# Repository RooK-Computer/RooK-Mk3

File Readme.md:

# RooK Mk3

RooK is a retro gaming console based on the Raspberry PI CM4. It has all the peripherials you need to be used as an old (modernish) console:

* HDMI for audio and video out.
* Barrel jack for 5V power input, because we love the simplicity of barrel jacks.
* an audio jack for, well... speakers!
* 4 USB ports for up to 4 modern gamepads.
* A cartridge slot!
* 3 Buttons to shut RooK down, exit the game and restart the game.

## How it all works

It's quite simple: instead of having an onboard SD card, the SD cards are installed onto separate PCBs for the cartridges. Once you put a cartridge in, RooK powers up and boots off the SD card in the cartridge.

Of course, unwrapping the SD cards can be tedious, so we built a cartridge reader.

It works out of the box with retropie, except for the three buttons. In this repository you find the software needed to enable those buttons. It's best done immediately after installing retropie, before you customize your setup.

## In this repository

There are 3 folders:

* software contains the sources for the .deb file to easily install overwatch and it's configuration. You'll find the .dep file in there as well, if you don't want to build it yourself. The source is compressed, as we have to ensure ownership and file privileges. Something git tends to ignore ;)
* PCBs contains all the designs for the PCBs involved: 
    * Cartridge - the PCB for cartridges
    * CartridgeReader - should be self-explanatory
    * KeyswitchCarrier - holds the switches for the three keys
    * Mainboard - the biggest of them.
    * Parts and CM4-Files are referenced in the aforementioned design files
* STLs contain the STL files for the case and the cartridge. You'll find our FreeCAD designs in there as well.

## I wanna build one!

Well for now, you have to produce and order the parts yourself. We're working on this. Stay tuned and keep an eye out at [rook.computer](https://rook.computer).

There is a building guide in the wiki.

## License

Unless noted otherwise this work is licensed under Creative Commons Attribution Share Alike 4.0 International.

`SPDX-License-Identifier:  CC-BY-SA-4.0`

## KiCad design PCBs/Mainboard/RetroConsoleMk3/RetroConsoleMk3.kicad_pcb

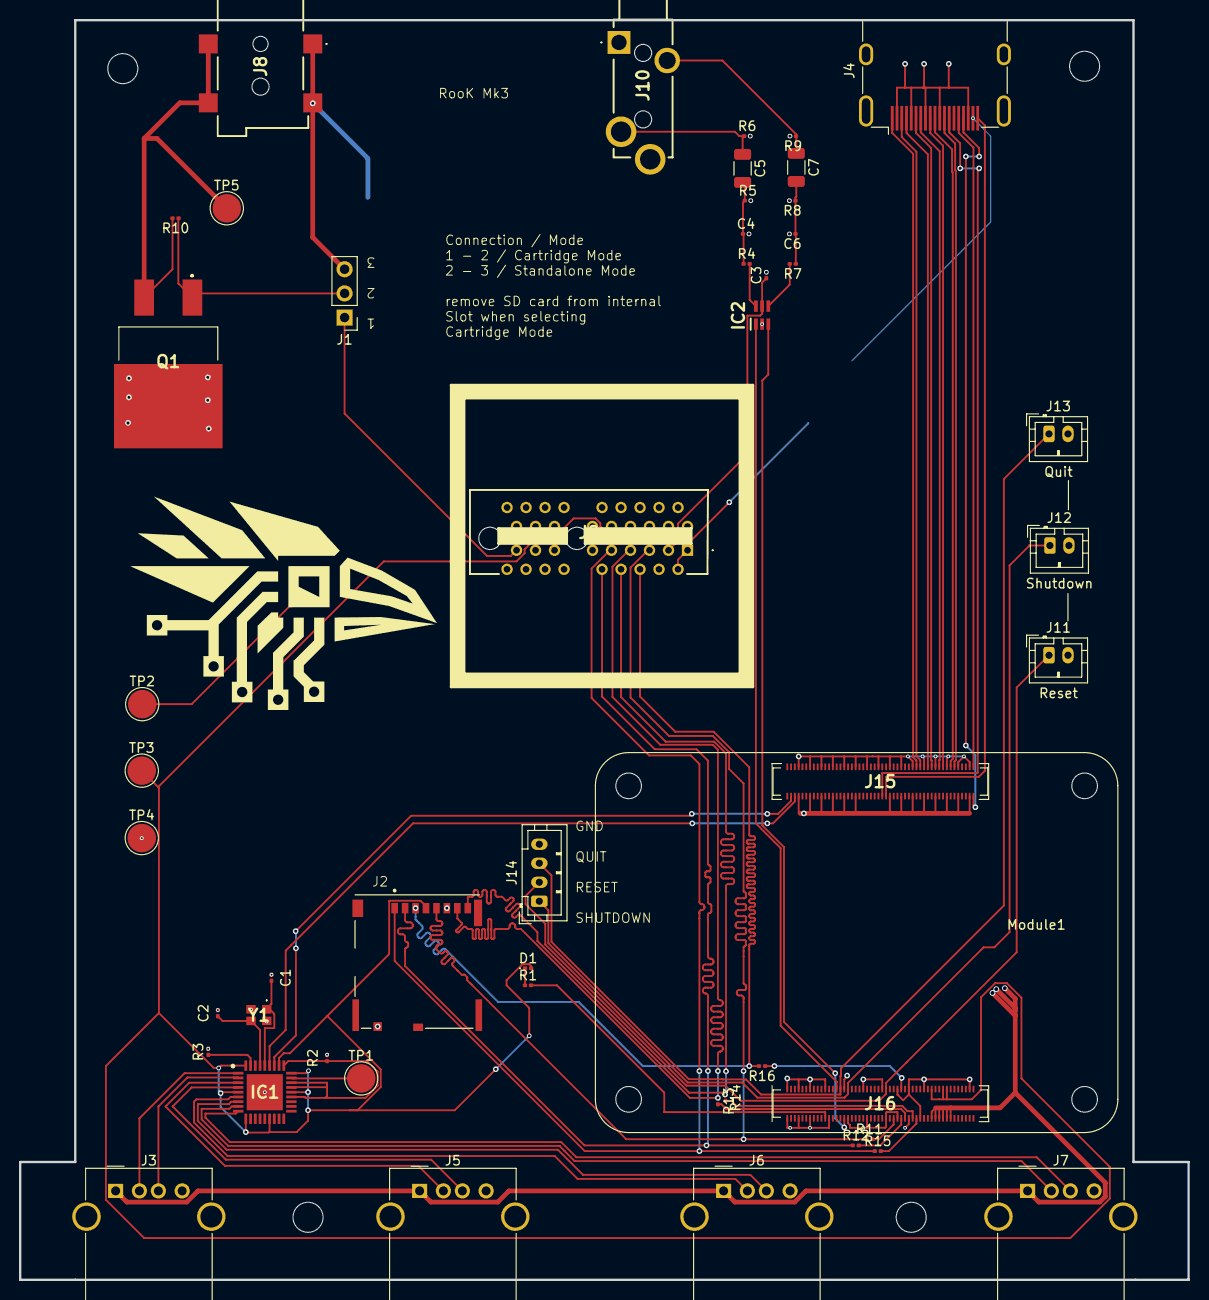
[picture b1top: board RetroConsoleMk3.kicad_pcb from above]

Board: 2 copper layers, 123.0 x 132.6 mm, 50 parts (0 on the bottom side), 58 nets.

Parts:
C1, C2: 14pF; C_0201_0603Metric
C3: 10nF; C_0201_0603Metric
C4, C6: 100nF; C_0201_0603Metric
C5, C7: 47uF; C_1206_3216Metric
D1: GREEN; LED_0201_0603Metric
IC1: USB2514B_M2; QFN50P600X600X100-37N-D
IC2: NC7WZ16P6X; SOT65P210X110-6N
J1: Conn_01x03_Socket; PinHeader_1x03_P2.54mm_Vertical
J2: Micro_SD_Card; SDCARD_MOLEX_503398-1892
J3, J5, J6, J7: USB_A; USB_A_Molex_67643_Horizontal
J4: HDMI_A_1.4; HDMI_A_Molex_208658-1001_Horizontal
J8: PJ-114AH-SMT-TR; PJ114AHSMTTR
J9: 1871058-1; 18710581
J10: SJ3-35083B-TR; SJ335083BTR
J11: Reset; JST_PH_B2B-PH-K_1x02_P2.00mm_Vertical
J12: Shutdown; JST_PH_B2B-PH-K_1x02_P2.00mm_Vertical
J13: Quit; JST_PH_B2B-PH-K_1x02_P2.00mm_Vertical
J14: Keys; JST_PH_B4B-PH-K_1x04_P2.00mm_Vertical
J15, J16: DF40C100DS04V51
Module1: ComputeModule4-CM4; Raspberry-Pi-4-Compute-Module
Q1: IRLZ34NSTRLPBF; IRF2804STRLPBF
R1: 1k; R_0201_0603Metric
R2: 100k; R_0201_0603Metric
R3: 12k (+/- 1%); R_0201_0603Metric
R4, R7: 220; R_0201_0603Metric
R5, R8: 100; R_0201_0603Metric
R6, R9: 1.8k; R_0201_0603Metric
R10: 10k; R_0201_0603Metric
R11, R12, R13, R14, R15, R16: 33; R_0201_0603Metric
TP1: USB RESET_N; TestPoint_Pad_D3.0mm
TP2: VCC; TestPoint_Pad_D3.0mm
TP3: 3V3; TestPoint_Pad_D3.0mm
TP4: GND; TestPoint_Pad_D3.0mm
TP5: GND_SUPPLY; TestPoint_Pad_D3.0mm
Y1: 830108208209

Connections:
3V3: C3.1, D1.2 (A), IC1.5 (VDDA33_1), IC1.10 (VDDA33_2), IC1.15 (VDD33_1), IC1.23 (VDD33_2), IC1.27 (VBUS_DET), IC1.29 (VDDA33_3), IC1.36 (VDDA33_4), IC2.5 (VCC), J2.4 (VDD), J9.A3, Module1.78 (GPIO_VREF(1.8v/3.3v_Input)), Module1.84 (+3.3v_(Output)), Module1.86 (+3.3v_(Output)), TP3.1
AUDIO_L: IC2.1 (A1), Module1.28 (GPIO13)
AUDIO_OUT_L: C5.1, J10.2 (TIP), R6.1
AUDIO_OUT_R: C7.1, J10.5 (RING), R9.1
AUDIO_R: IC2.3 (A2), Module1.31 (GPIO12)
CARD_PRESENT: J1.1, J9.A17
GND: C1.1, C2.2, C3.2, C4.2, C6.2, IC1.37 (EP), IC2.2 (GND), J2.6 (VSS), J2.9 (SHIELD), J3.4 (GND), J3.5 (Shield), J4.2 (D2S), J4.5 (D1S), J4.8 (D0S), J4.11 (CKS), J4.17 (GND), J5.4 (GND), J5.5 (Shield), J6.4 (GND), J6.5 (Shield), J7.4 (GND), J7.5 (Shield), J9.A4, J9.B1, J9.B2, J9.B3, J9.B4, J9.B5, J9.B6, J9.B7, J9.B8, J9.B9, J9.B10, J10.1 (SLEEVE), J11.2, J12.2, J13.2, J14.4, Module1.1 (GND), Module1.2 (GND), Module1.7 (GND), Module1.8 (GND), Module1.13 (GND), Module1.14 (GND), Module1.22 (GND), Module1.23 (GND), Module1.32 (GND), Module1.33 (GND), Module1.42 (GND), Module1.43 (GND), Module1.52 (GND), Module1.53 (GND), Module1.59 (GND), Module1.60 (GND), Module1.65 (GND), Module1.66 (GND), Module1.71 (GND), Module1.74 (GND), Module1.98 (GND), Module1.107 (GND), Module1.108 (GND), Module1.113 (GND), Module1.114 (GND), Module1.119 (GND), Module1.120 (GND), Module1.125 (GND), Module1.126 (GND), Module1.131 (GND), Module1.132 (GND), Module1.137 (GND), Module1.138 (GND), Module1.144 (GND), Module1.150 (GND), Module1.155 (GND), Module1.156 (GND), Module1.161 (GND), Module1.162 (GND), Module1.167 (GND), Module1.168 (GND), Module1.173 (GND), Module1.174 (GND), Module1.179 (GND), Module1.180 (GND), Module1.185 (GND), Module1.186 (GND), Module1.191 (GND), Module1.192 (GND), Module1.197 (GND), Module1.198 (GND), Q1.2 (D), R2.2, R3.2, R5.2, R6.2, R8.2, R9.2, TP4.1, Y1.2 (GND_1), Y1.4 (GND_2)
GND_SUPPLY: J8.2, J8.3, Q1.3 (S), R10.2, TP5.1
GPIO4: J11.1, J14.2, Module1.54 (GPIO4)
GPIO5: J12.1, J14.1, Module1.34 (GPIO5)
GPIO6: J13.1, J14.3, Module1.30 (GPIO6)
HDMI_CEC: J4.13 (CEC), Module1.151 (HDMI0_CEC)
HDMI_CK+: J4.10 (CK+), Module1.188 (HDMI0_CLK_P)
HDMI_CK-: J4.12 (CK-), Module1.190 (HDMI0_CLK_N)
HDMI_D0+: J4.7 (D0+), Module1.182 (HDMI0_TX0_P)
HDMI_D0-: J4.9 (D0-), Module1.184 (HDMI0_TX0_N)
HDMI_D1+: J4.4 (D1+), Module1.176 (HDMI0_TX1_P)
HDMI_D1-: J4.6 (D1-), Module1.178 (HDMI0_TX1_N)
HDMI_D2+: J4.1 (D2+), Module1.170 (HDMI0_TX2_P)
HDMI_D2-: J4.3 (D2-), Module1.172 (HDMI0_TX2_N)
HDMI_HEAC-: J4.19 (HPD/HEAC-), Module1.153 (HDMI0_HOTPLUG)
HDMI_SCL: J4.15 (SCL), Module1.200 (HDMI0_SCL)
HDMI_SDA: J4.16 (SDA), Module1.199 (HDMI0_SDA)
LED_ACTIVITY: Module1.21 (PI_nLED_Activity), R1.2
unnamed: C4.1, C5.2, R4.1, R5.1
unnamed: C6.1, C7.2, R7.1, R8.1
unnamed: D1.1 (K), R1.1
unnamed: IC1.26 (RESET_N), TP1.1
unnamed: IC1.1 (USBDM_DN1/PRT_DIS_M1), J3.2 (D-)
unnamed: IC1.3 (USBDM_DN2/PRT_DIS_M2), J5.2 (D-)
unnamed: IC1.6 (USBDM_DN3/PRT_DIS_M3), J6.2 (D-)
unnamed: IC1.8 (USBDM_DN4/PRT_DIS_M4), J7.2 (D-)
unnamed: IC1.2 (USBDP_DN1/PRT_DIS_P1), J3.3 (D+)
unnamed: IC1.4 (USBDP_DN2/PRT_DIS_P2), J5.3 (D+)
unnamed: IC1.7 (USBDP_DN3/PRT_DIS_P3), J6.3 (D+)
unnamed: IC1.9 (USBDP_DN4/PRT_DIS_P4), J7.3 (D+)
unnamed: IC2.6 (Y1), R4.2
unnamed: IC2.4 (Y2), R7.2
unnamed: Module1.57 (SD_CLK), R11.2
unnamed: Module1.62 (SD_CMD), R16.1
unnamed: Module1.63 (SD_DAT0), R13.2
unnamed: Module1.67 (SD_DAT1), R14.2
unnamed: Module1.69 (SD_DAT2), R15.2
unnamed: Module1.61 (SD_DAT3), R12.2
SD_CLK: J2.5 (CLK), J9.A5, R11.1
SD_CMD: J2.3 (CMD), J9.A6, R16.2
SD_DAT0: J2.7 (DAT0), J9.A7, R13.1
SD_DAT1: J2.8 (DAT1), J9.A8, R14.1
SD_DAT2: J2.1 (DAT2), J9.A9, R15.1
SD_DAT3: J2.2 (DAT3/CD), J9.A10, R12.1
SUPPLY_ENABLE: J1.2, Q1.1 (G), R10.1
USB_CFG_SEL0: IC1.22 (SDA/SMBDATA/NONREM1), IC1.24 (SCL/SMBCLK/CFG_SEL0), IC1.25 (HS_IND/CFG_SEL1), IC1.28 (SUSP_IND/LOCAL_PWR/NON_REM0), R2.1
USB_D+: IC1.31 (USBDP_UP), Module1.105 (USB2_P)
USB_D-: IC1.30 (USBDM_UP), Module1.103 (USB2_N)
USB_RBIAS: IC1.35 (RBIAS), R3.1
USB_XTAL_IN: C2.1, IC1.33 (XTALIN/CLKIN), Y1.3 (CRYSTAL_2)
USB_XTAL_OUT: C1.2, IC1.32 (XTALOUT), Y1.1 (CRYSTAL_1)
VCC: J1.3, J3.1 (VBUS), J4.18 (+5V), J5.1 (VBUS), J6.1 (VBUS), J7.1 (VBUS), J8.A1, J8.B1, J9.A1, J9.A2, Module1.77 (+5v_(Input)), Module1.79 (+5v_(Input)), Module1.81 (+5v_(Input)), Module1.83 (+5v_(Input)), Module1.85 (+5v_(Input)), Module1.87 (+5v_(Input)), TP2.1

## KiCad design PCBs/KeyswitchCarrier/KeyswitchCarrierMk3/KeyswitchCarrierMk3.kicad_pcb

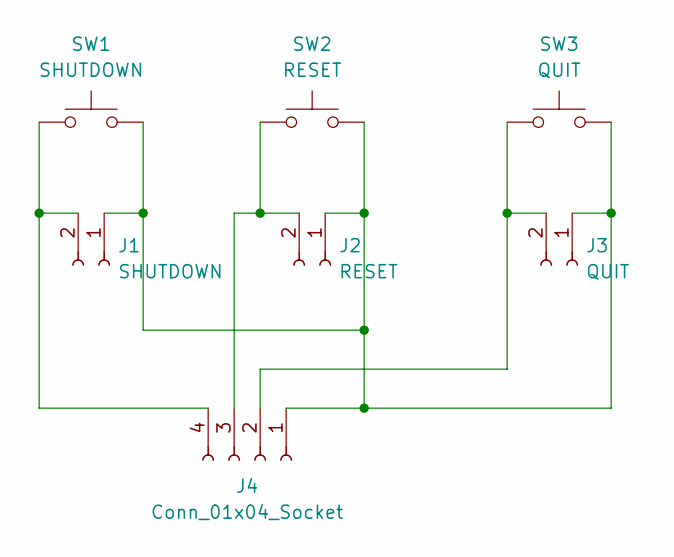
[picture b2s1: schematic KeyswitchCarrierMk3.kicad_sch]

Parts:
J1: SHUTDOWN; JST_PH_S2B-PH-K_1x02_P2.00mm_Horizontal
J2: RESET; JST_PH_S2B-PH-K_1x02_P2.00mm_Horizontal
J3: QUIT; JST_PH_S2B-PH-K_1x02_P2.00mm_Horizontal
J4: Conn_01x04_Socket; JST_PH_S4B-PH-K_1x04_P2.00mm_Horizontal
SW1: SHUTDOWN; SW_Cherry_MX_1.00u_PCB
SW2: RESET; SW_Cherry_MX_1.00u_PCB
SW3: QUIT; SW_Cherry_MX_1.00u_PCB

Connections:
unnamed: J1.1, J2.1, J3.1, J4.1, SW1.2, SW2.2, SW3.2
unnamed: J1.2, J4.4, SW1.1
unnamed: J2.2, J4.3, SW2.1
unnamed: J3.2, J4.2, SW3.1

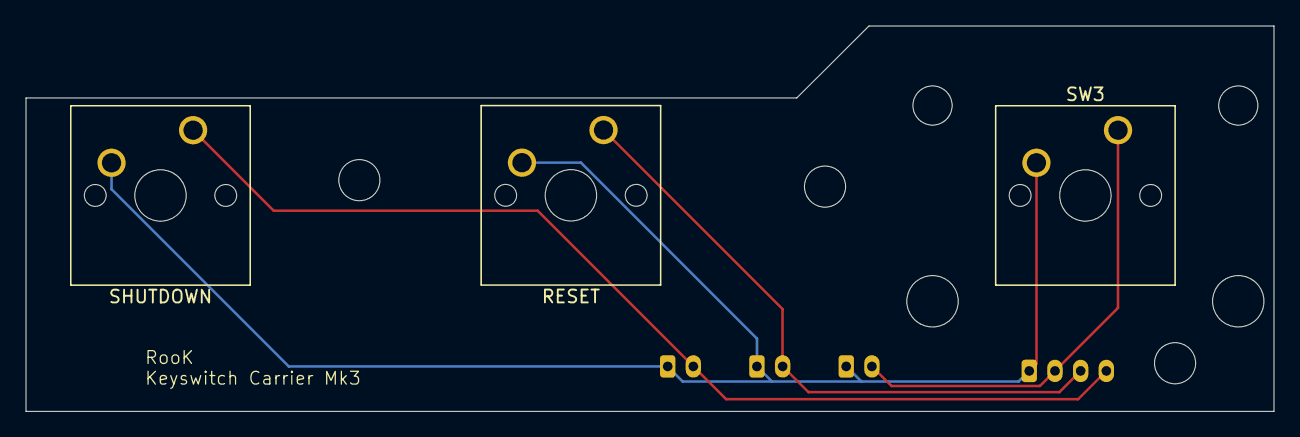
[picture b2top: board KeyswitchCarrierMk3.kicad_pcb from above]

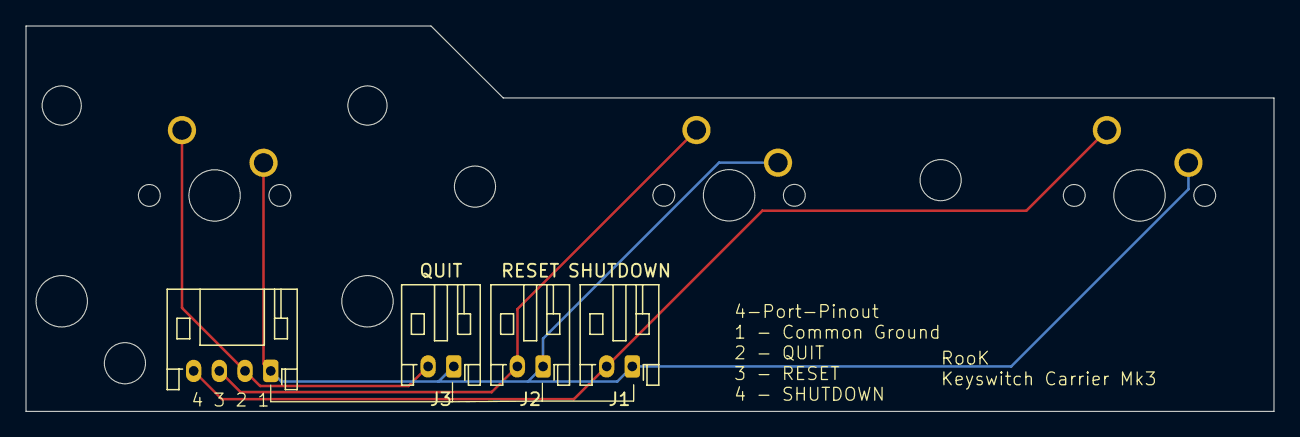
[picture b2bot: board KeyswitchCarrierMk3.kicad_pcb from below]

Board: 2 copper layers, 97.1 x 30.0 mm, 7 parts (4 on the bottom side), 4 nets.

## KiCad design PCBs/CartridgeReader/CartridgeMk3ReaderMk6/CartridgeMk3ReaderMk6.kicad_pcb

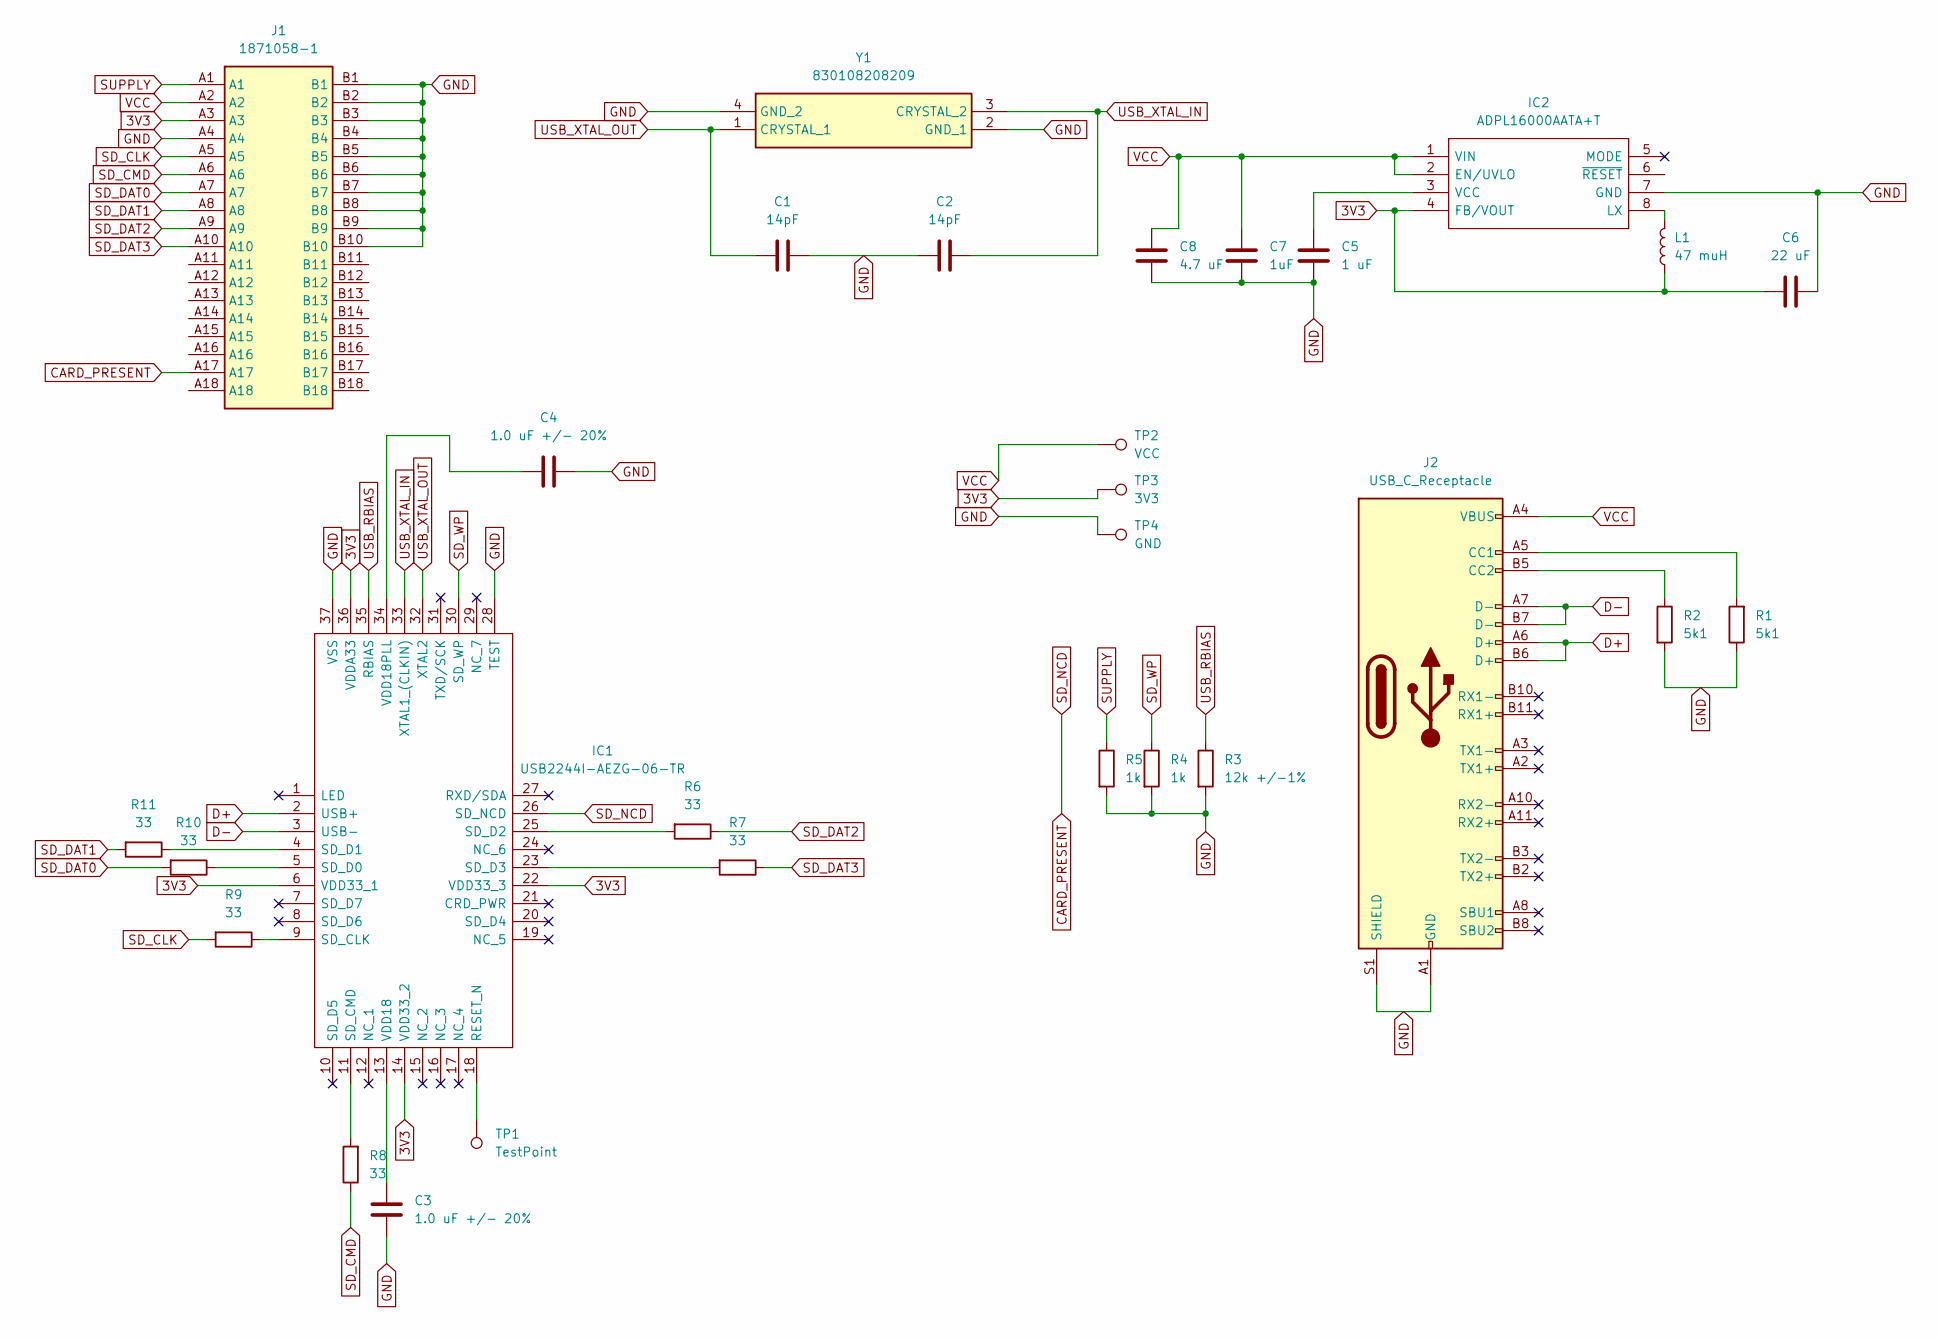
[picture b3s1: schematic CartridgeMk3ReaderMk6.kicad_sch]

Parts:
C1, C2: 14pF; C_0201_0603Metric
C3, C4: 1.0 uF +/- 20%; C_0201_0603Metric
C5: 1 uF; C_0201_0603Metric
C6: 22 uF; C_1206_3216Metric
C7: 1uF; C_1206_3216Metric
C8: 4.7 uF; C_1206_3216Metric
IC1: USB2244I-AEZG-06-TR; QFN50P600X600X90-37N-D; Manufacturer_Part_Number USB2244I-AEZG-06-TR; Mouser Part Number 579-USB2244IAEZG06TR
IC2: ADPL16000AATA+T; ADPL16000AATAT; Manufacturer_Part_Number ADPL16000AATA+T; Mouser Part Number 700-ADPL16000AATA+T
J1: 1871058-1; 18710581; Manufacturer_Part_Number 1871058-1; Mouser Part Number 571-1871058-1
J2: USB_C_Receptacle; USB_C_Receptacle_Molex_105450-0101
L1: 47 muH; 74404054470
R1, R2: 5k1; R_0201_0603Metric
R3: 12k +/-1%; R_0201_0603Metric
R4, R5: 1k; R_0201_0603Metric
R6, R7, R8, R9, R10, R11: 33; R_0201_0603Metric
TP1: TestPoint; TestPoint_Pad_D3.0mm
TP2: VCC; TestPoint_Pad_D3.0mm
TP3: 3V3; TestPoint_Pad_D3.0mm
TP4: GND; TestPoint_Pad_D3.0mm
Y1: 830108208209; Manufacturer_Part_Number 830108208209; Mouser Part Number 710-830108208209

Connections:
3V3: C6.2, IC1.6 (VDD33_1), IC1.14 (VDD33_2), IC1.22 (VDD33_3), IC1.36 (VDDA33), IC2.4 (FB/VOUT), J1.A3, L1.1, TP3.1
CARD_PRESENT: IC1.26 (SD_NCD), J1.A17
D+: IC1.2 (USB+), J2.A6 (D+), J2.B6 (D+)
D-: IC1.3 (USB-), J2.A7 (D-), J2.B7 (D-)
GND: C1.1, C2.2, C3.2, C4.2, C5.2, C6.1, C7.2, C8.1, IC1.28 (TEST), IC1.37 (VSS), IC2.7 (GND), J1.A4, J1.B1, J1.B2, J1.B3, J1.B4, J1.B5, J1.B6, J1.B7, J1.B8, J1.B9, J1.B10, J2.A1 (GND), J2.A12 (GND), J2.B1 (GND), J2.B12 (GND), J2.S1 (SHIELD), R1.1, R2.2, R3.2, R4.2, R5.2, TP4.1, Y1.2 (GND_1), Y1.4 (GND_2)
unnamed: IC1.18 (RESET_N), TP1.1
unnamed: IC1.9 (SD_CLK), R9.1
unnamed: IC1.11 (SD_CMD), R8.2
unnamed: IC1.5 (SD_D0), R10.1
unnamed: IC1.4 (SD_D1), R11.1
unnamed: IC1.25 (SD_D2), R6.2
unnamed: IC1.23 (SD_D3), R7.2
unnamed: C3.1, IC1.13 (VDD18)
unnamed: C4.1, IC1.34 (VDD18PLL)
unnamed: IC2.8 (LX), L1.2
unnamed: C5.1, IC2.3 (VCC)
unnamed: J2.A5 (CC1), R1.2
unnamed: J2.B5 (CC2), R2.1
SD_CLK: J1.A5, R9.2
SD_CMD: J1.A6, R8.1
SD_DAT0: J1.A7, R10.2
SD_DAT1: J1.A8, R11.2
SD_DAT2: J1.A9, R6.1
SD_DAT3: J1.A10, R7.1
SD_WP: IC1.30 (SD_WP), R4.1
SUPPLY: J1.A1, R5.1
USB_RBIAS: IC1.35 (RBIAS), R3.1
USB_XTAL_IN: C2.1, IC1.33 (XTAL1_(CLKIN)), Y1.3 (CRYSTAL_2)
USB_XTAL_OUT: C1.2, IC1.32 (XTAL2), Y1.1 (CRYSTAL_1)
VCC: C7.1, C8.2, IC2.1 (VIN), IC2.2 (EN/UVLO), J1.A2, J2.A4 (VBUS), J2.A9 (VBUS), J2.B4 (VBUS), J2.B9 (VBUS), TP2.1

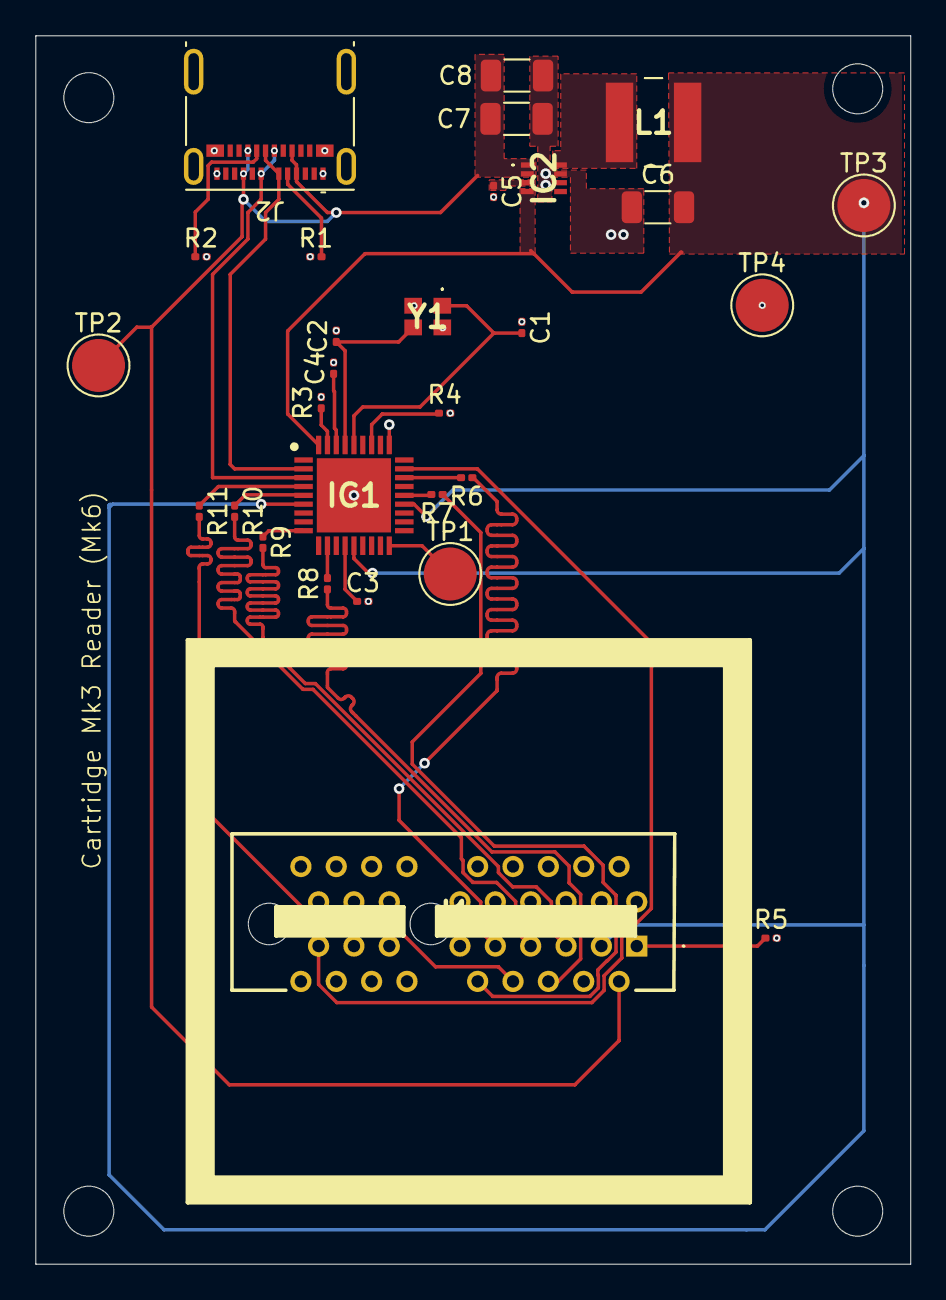
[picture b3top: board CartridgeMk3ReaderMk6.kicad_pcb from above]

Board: 2 copper layers, 49.5 x 69.5 mm, 29 parts (0 on the bottom side), 30 nets.

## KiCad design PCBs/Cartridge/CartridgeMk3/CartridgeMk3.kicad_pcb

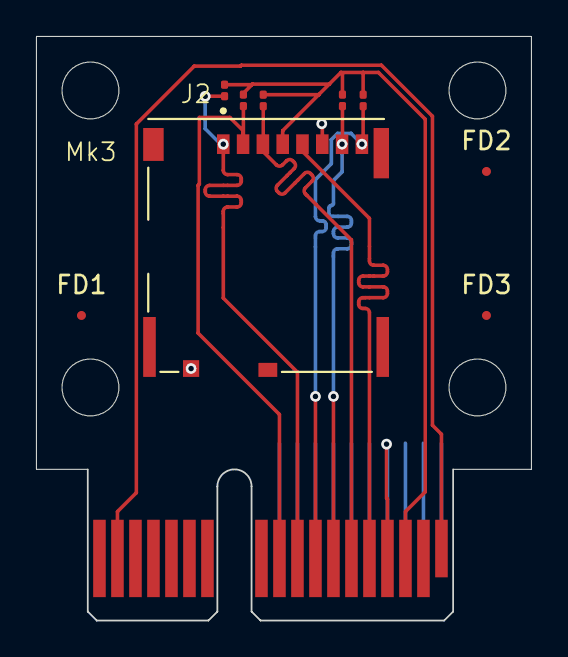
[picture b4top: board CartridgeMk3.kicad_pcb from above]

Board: 2 copper layers, 27.5 x 32.5 mm, 10 parts (1 on the bottom side), 9 nets.

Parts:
FD1, FD2, FD3: Fiducial_0.5mm_Mask1.5mm
J1: CartridgeConnMk1; BUS_PCIexpress_x1
J2: Micro_SD_Card; SDCARD_MOLEX_503398-1892
R1, R2, R3, R4, R5: 10k; R_0201_0603Metric

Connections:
3V3: J1.A3 (+3.3V), J2.4 (VDD), R1.1, R2.1, R3.1, R4.1, R5.1
GND: J1.A4 (GND), J1.B1 (GND), J1.B2 (GND), J1.B3 (GND), J1.B4 (GND), J1.B5 (GND), J1.B6 (GND), J1.B7 (GND), J1.B8 (GND), J1.B9 (GND), J1.B10 (GND), J2.6 (VSS), J2.9 (SHIELD)
unnamed: J1.A1 (SUPPLY), J1.A17 (CARD_PRESENT)
SD_CLK: J1.A5 (SD_CLK), J2.5 (CLK)
SD_CMD: J1.A6 (SD_CMD), J2.3 (CMD), R4.2
SD_DAT0: J1.A7 (SD_DAT0), J2.7 (DAT0), R2.2
SD_DAT1: J1.A8 (SD_DAT1), J2.8 (DAT1), R1.2
SD_DAT2: J1.A9 (SD_DAT2), J2.1 (DAT2), R3.2
SD_DAT3: J1.A10 (SD_DAT3), J2.2 (DAT3/CD), R5.2

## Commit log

2025-05-22 first version of overwatch for rook mk2 fully configured and working.
2025-09-12 added the dependencies of our pcb designs
2025-09-12 added cartridge pcb design
2025-09-12 added cartridge reader pcb design
2025-09-12 added keyswitch carrier pcb design
2025-09-12 added the Mk3 mainboard pcb design
2025-09-12 added gitignore
2025-09-12 added CAD files and STL exports
2025-09-12 added readme.
2025-09-18 updated cartridge case files
    Fine-tuned the top part of the cartridge to increase clamping forces of
    things someone might add to the cartridge.
2025-09-19 removed redundand (old) button versions.
2025-09-19 tuned the quit button for better snap-fit.
2025-09-20 updated parts of the keys
2026-01-14 Add LICENSE
